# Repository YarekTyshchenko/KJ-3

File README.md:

KJ-3
====
Programming ATMega328 using an Arduino Micro
--------------------------------------------

All tutorials around programming ATMegas seem to revolve around removing the MCU from
an Arduino Uno and flashing it using normal methods. Since I don't have an Uno, and I
don't plan on getting one, it doesn't fit my needs, I need something that can go into
a breadboard, i've been having a really hard time collecting all the information on
making it work with a Micro and ISCP

So far i've got a few bits of information:

1. Upload ArduinoISP to your Mega, changing the SS definition to pin 10.
1. Modify boards.txt to include your breadboard configuration, or use Arduino Due 328
1. Add ArduinoISP as Micro definition to programmers.txt, found online somehwere
1. Compile and burn the chip with Shift+Ctrl-U (Shift click upload) to use the programmer...

This results in the code running on your new breadboarded MCU!

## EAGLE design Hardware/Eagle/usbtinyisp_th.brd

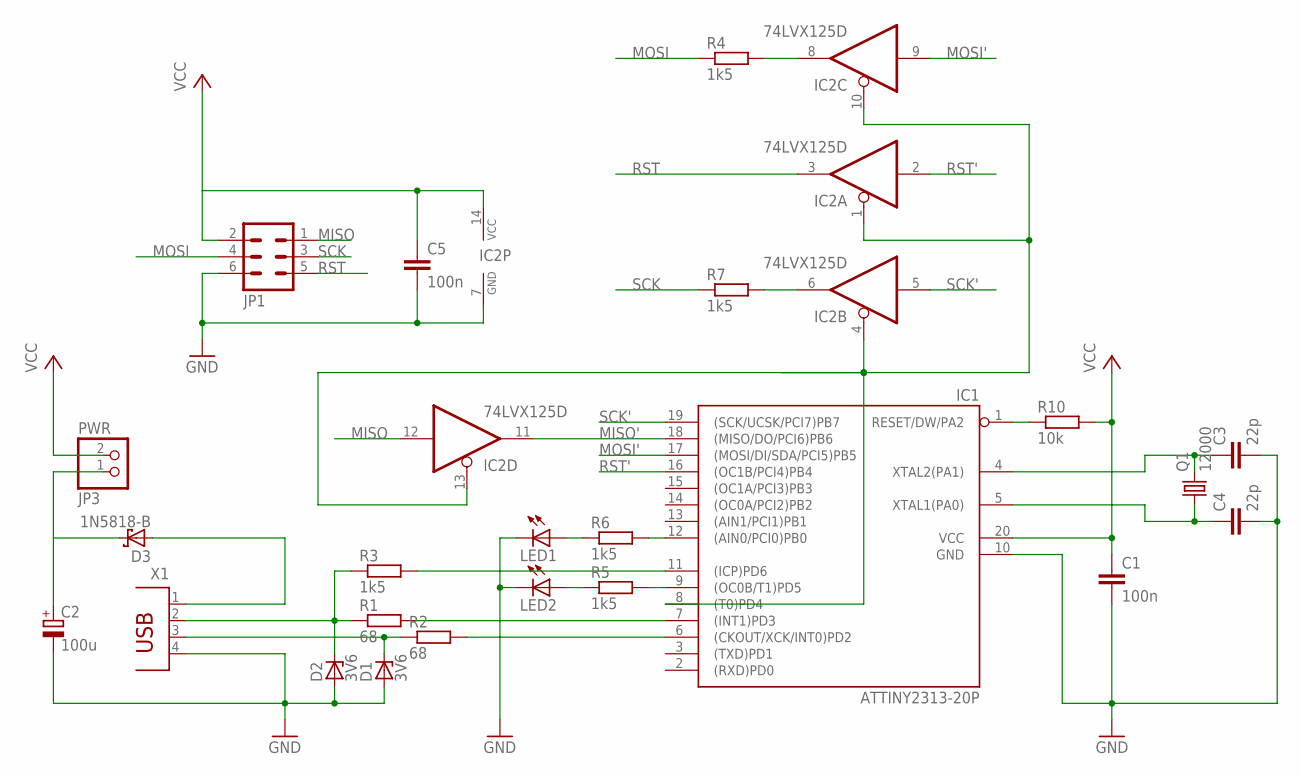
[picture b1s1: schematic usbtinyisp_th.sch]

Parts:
C1, C5: 100n; C025-025X050
C2: 100u; E2,5-6
C3, C4: 22p; C025-025X050
D1, D2: 3V6; DO35Z10
D3: 1N5818-B; DO41-7.6
IC1: ATTINY2313-20P; DIL20
IC2: 74LVX125D; DIL14
JP1: MA03-2
JP3: PWR; 1X02
LED1, LED2: LED5MM
Q1: 12000; HC49U-V
R1, R2: 68; 0204/7
R3, R4, R5, R6, R7: 1k5; 0204/7
R10: 10k; 0204/7
X1: PN61729

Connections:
GND: C1.2, C2.-, C3.2, C4.2, C5.2, D1.A, D2.A, IC1.10 (GND), IC2.7 (GND), JP1.6, LED1.K (C), LED2.K (C), X1.4
MISO: IC2.12 (I), JP1.1
MISO': IC1.18 ((MISO/DO/PCI6)PB6), IC2.11 (O)
MOSI: JP1.4, R4.1
MOSI': IC1.17 ((MOSI/DI/SDA/PCI5)PB5), IC2.9 (I)
unnamed: D2.C, R1.1, R3.1, X1.2
unnamed: D1.C, R2.1, X1.3
unnamed: IC1.7 ((INT1)PD3), R1.2
unnamed: C2.+, D3.C, JP3.1
unnamed: LED1.A, R6.1
unnamed: IC1.6 ((CKOUT/XCK/INT0)PD2), R2.2
unnamed: IC1.12 ((AIN0/PCI0)PB0), R6.2
unnamed: IC1.1 (RESET/DW/PA2), R10.1
unnamed: IC1.9 ((OC0B/T1)PD5), R5.2
unnamed: LED2.A, R5.1
unnamed: IC2.6 (O), R7.2
unnamed: IC2.8 (O), R4.2
unnamed: IC1.8 ((T0)PD4), IC2.1 (OE), IC2.4 (OE), IC2.10 (OE), IC2.13 (OE)
unnamed: IC1.11 ((ICP)PD6), R3.2
RST: IC2.3 (O), JP1.5
RST': IC1.16 ((OC1B/PCI4)PB4), IC2.2 (I)
SCK: JP1.3, R7.1
SCK': IC1.19 ((SCK/UCSK/PCI7)PB7), IC2.5 (I)
VBUS: D3.A, X1.1
VCC: C1.1, C5.1, IC1.20 (VCC), IC2.14 (VCC), JP1.2, JP3.2, R10.2
XTAL1: C4.1, IC1.5 (XTAL1(PA0)), Q1.1
XTAL2: C3.1, IC1.4 (XTAL2(PA1)), Q1.2

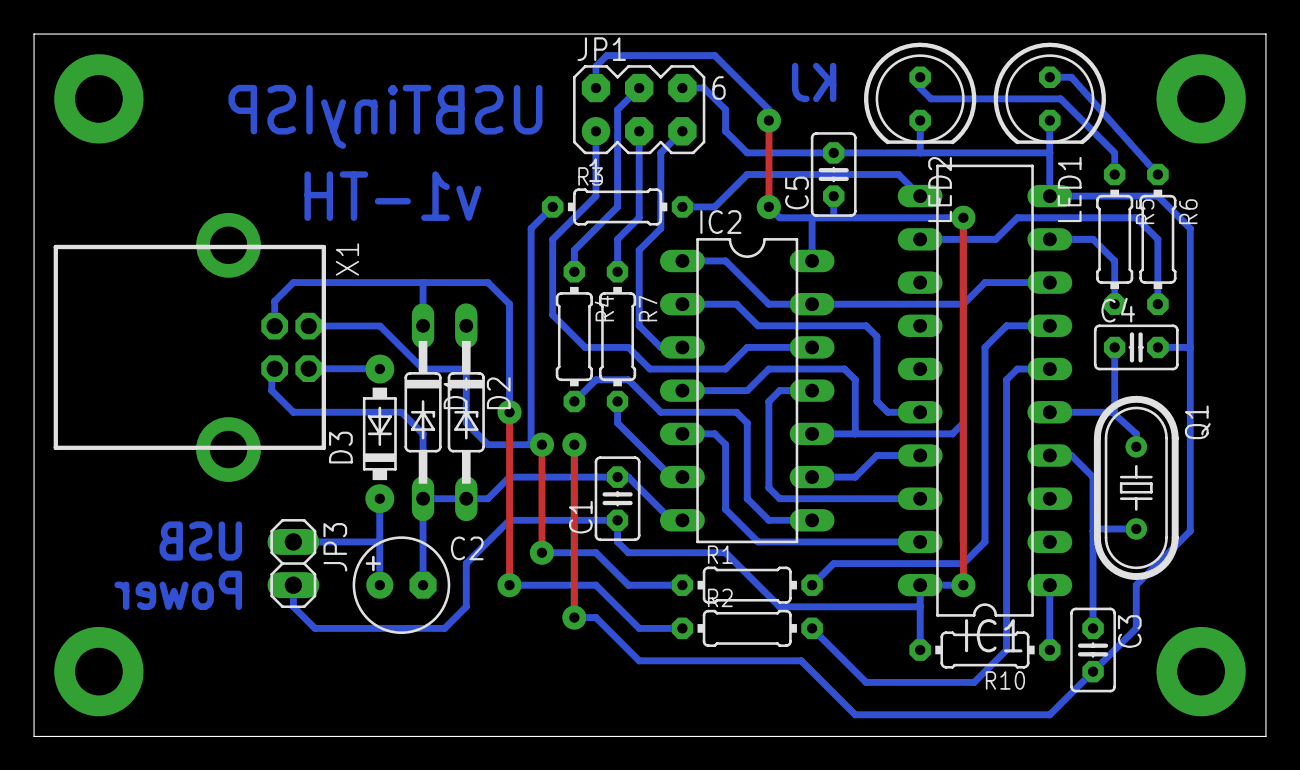
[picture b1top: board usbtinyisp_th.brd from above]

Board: 2 copper layers, 72.4 x 41.3 mm, 24 parts (0 on the bottom side), 27 nets.

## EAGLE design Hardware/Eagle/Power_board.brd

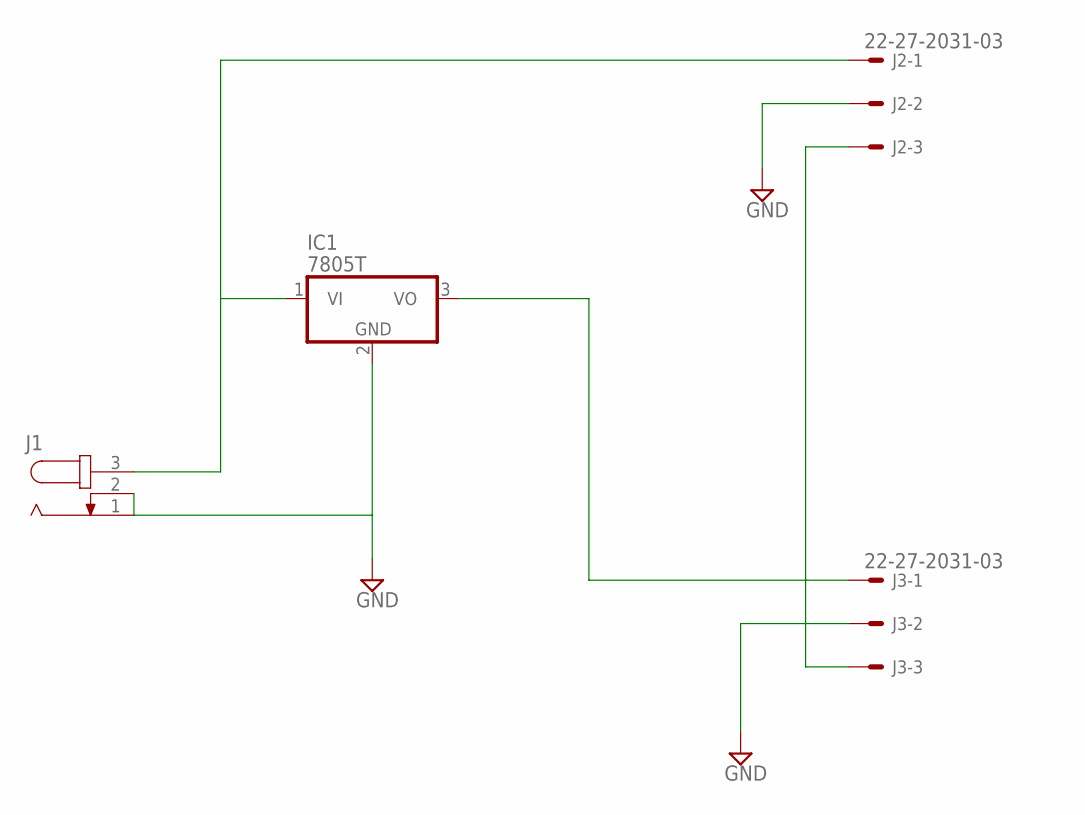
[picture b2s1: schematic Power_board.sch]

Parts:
IC1: 7805T; TO220H
J1: JACK-PLUG0; SPC4077
J2, J3: 22-27-2031-03; 6410-03

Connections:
GND: IC1.2 (GND), J1.1, J1.2, J2.2, J3.2
unnamed: IC1.1 (VI), J1.3, J2.1
unnamed: J2.3, J3.3
unnamed: IC1.3 (VO), J3.1

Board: 2 copper layers, 4 parts (0 on the bottom side), 4 nets, no tracks yet.

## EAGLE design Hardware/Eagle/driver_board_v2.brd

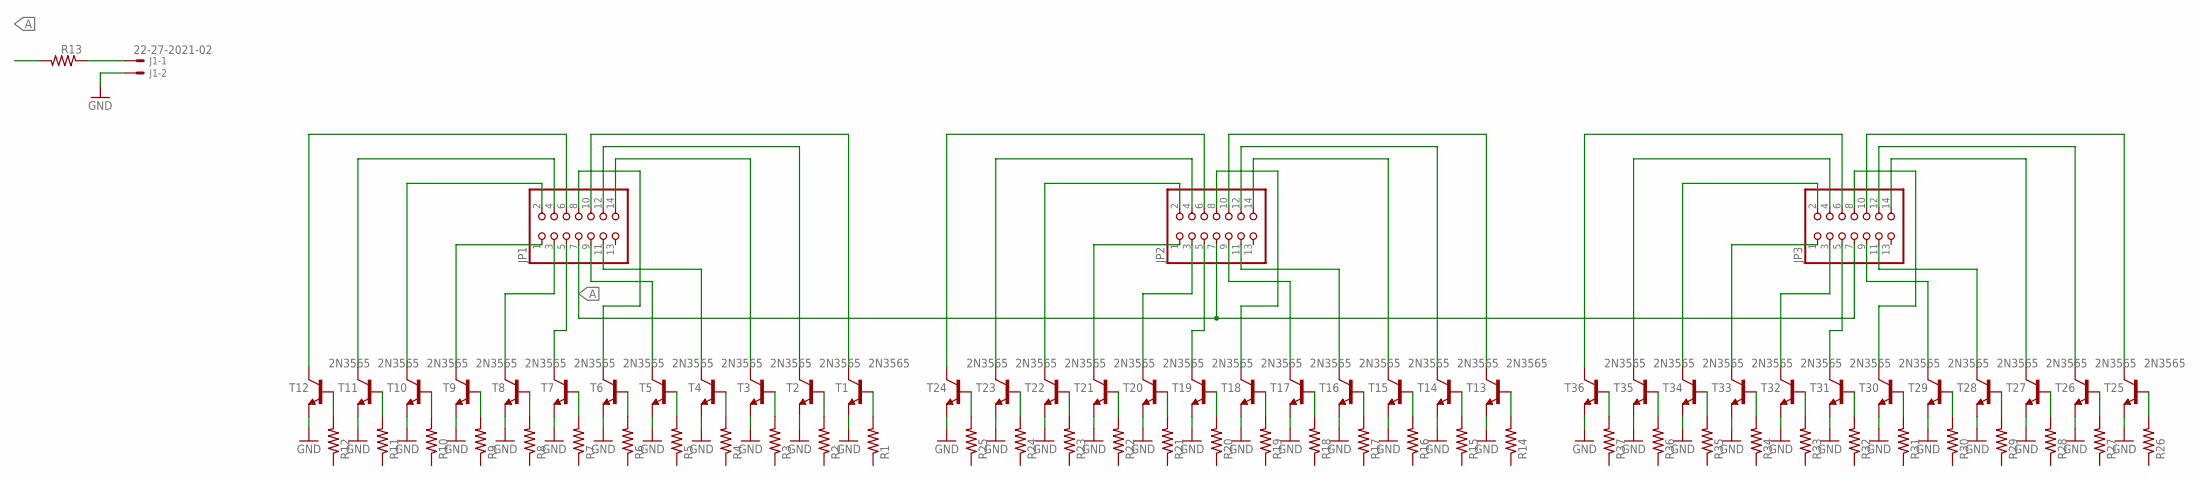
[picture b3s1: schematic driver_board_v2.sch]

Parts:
J1: 22-27-2021-02; 6410-02
JP1, JP2, JP3: PINHD-2X7; 2X07
R1, R2, R3, R4, R5, R6, R7, R8, R9, R10, R11, R12, R13, R14, R15, R16, R17, R18, R19, R20, R21, R22, R23, R24, R25, R26, R27, R28, R29, R30, R31, R32, R33, R34, R35, R36, R37: R-US_0204/7; 0204/7
T1, T2, T3, T4, T5, T6, T7, T8, T9, T10, T11, T12, T13, T14, T15, T16, T17, T18, T19, T20, T21, T22, T23, T24, T25, T26, T27, T28, T29, T30, T31, T32, T33, T34, T35, T36: 2N3565; TO92

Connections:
GND: J1.2, T1.3 (E), T2.3 (E), T3.3 (E), T4.3 (E), T5.3 (E), T6.3 (E), T7.3 (E), T8.3 (E), T9.3 (E), T10.3 (E), T11.3 (E), T12.3 (E), T13.3 (E), T14.3 (E), T15.3 (E), T16.3 (E), T17.3 (E), T18.3 (E), T19.3 (E), T20.3 (E), T21.3 (E), T22.3 (E), T23.3 (E), T24.3 (E), T25.3 (E), T26.3 (E), T27.3 (E), T28.3 (E), T29.3 (E), T30.3 (E), T31.3 (E), T32.3 (E), T33.3 (E), T34.3 (E), T35.3 (E), T36.3 (E)
unnamed: R12.2, T12.2 (B)
unnamed: R11.2, T11.2 (B)
unnamed: R10.2, T10.2 (B)
unnamed: R9.2, T9.2 (B)
unnamed: R8.2, T8.2 (B)
unnamed: R7.2, T7.2 (B)
unnamed: R6.2, T6.2 (B)
unnamed: R5.2, T5.2 (B)
unnamed: R4.2, T4.2 (B)
unnamed: R3.2, T3.2 (B)
unnamed: R2.2, T2.2 (B)
unnamed: R1.2, T1.2 (B)
unnamed: JP1.6, T12.1 (C)
unnamed: JP1.4, T11.1 (C)
unnamed: JP1.2, T10.1 (C)
unnamed: JP1.1, T9.1 (C)
unnamed: JP1.3, T8.1 (C)
unnamed: JP1.5, T7.1 (C)
unnamed: JP1.10, T1.1 (C)
unnamed: JP1.12, T2.1 (C)
unnamed: JP1.14, T3.1 (C)
unnamed: JP1.8, T6.1 (C)
unnamed: JP1.9, T5.1 (C)
unnamed: JP1.11, T4.1 (C)
unnamed: J1.1, R13.1
unnamed: R25.2, T24.2 (B)
unnamed: R24.2, T23.2 (B)
unnamed: R23.2, T22.2 (B)
unnamed: R22.2, T21.2 (B)
unnamed: R21.2, T20.2 (B)
unnamed: R20.2, T19.2 (B)
unnamed: R19.2, T18.2 (B)
unnamed: R18.2, T17.2 (B)
unnamed: R17.2, T16.2 (B)
unnamed: R16.2, T15.2 (B)
unnamed: R15.2, T14.2 (B)
unnamed: R14.2, T13.2 (B)
unnamed: JP2.6, T24.1 (C)
unnamed: JP2.4, T23.1 (C)
unnamed: JP2.2, T22.1 (C)
unnamed: JP2.1, T21.1 (C)
unnamed: JP2.3, T20.1 (C)
unnamed: JP2.5, T19.1 (C)
unnamed: JP2.10, T13.1 (C)
unnamed: JP2.12, T14.1 (C)
unnamed: JP2.14, T15.1 (C)
unnamed: JP2.8, T18.1 (C)
unnamed: JP2.9, T17.1 (C)
unnamed: JP2.11, T16.1 (C)
unnamed: R37.2, T36.2 (B)
unnamed: R36.2, T35.2 (B)
unnamed: R35.2, T34.2 (B)
unnamed: R34.2, T33.2 (B)
unnamed: R33.2, T32.2 (B)
unnamed: R32.2, T31.2 (B)
unnamed: R31.2, T30.2 (B)
unnamed: R30.2, T29.2 (B)
unnamed: R29.2, T28.2 (B)
unnamed: R28.2, T27.2 (B)
unnamed: R27.2, T26.2 (B)
unnamed: R26.2, T25.2 (B)
unnamed: JP3.6, T36.1 (C)
unnamed: JP3.4, T35.1 (C)
unnamed: JP3.2, T34.1 (C)
unnamed: JP3.1, T33.1 (C)
unnamed: JP3.3, T32.1 (C)
unnamed: JP3.5, T31.1 (C)
unnamed: JP3.10, T25.1 (C)
unnamed: JP3.12, T26.1 (C)
unnamed: JP3.14, T27.1 (C)
unnamed: JP3.8, T30.1 (C)
unnamed: JP3.9, T29.1 (C)
unnamed: JP3.11, T28.1 (C)

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
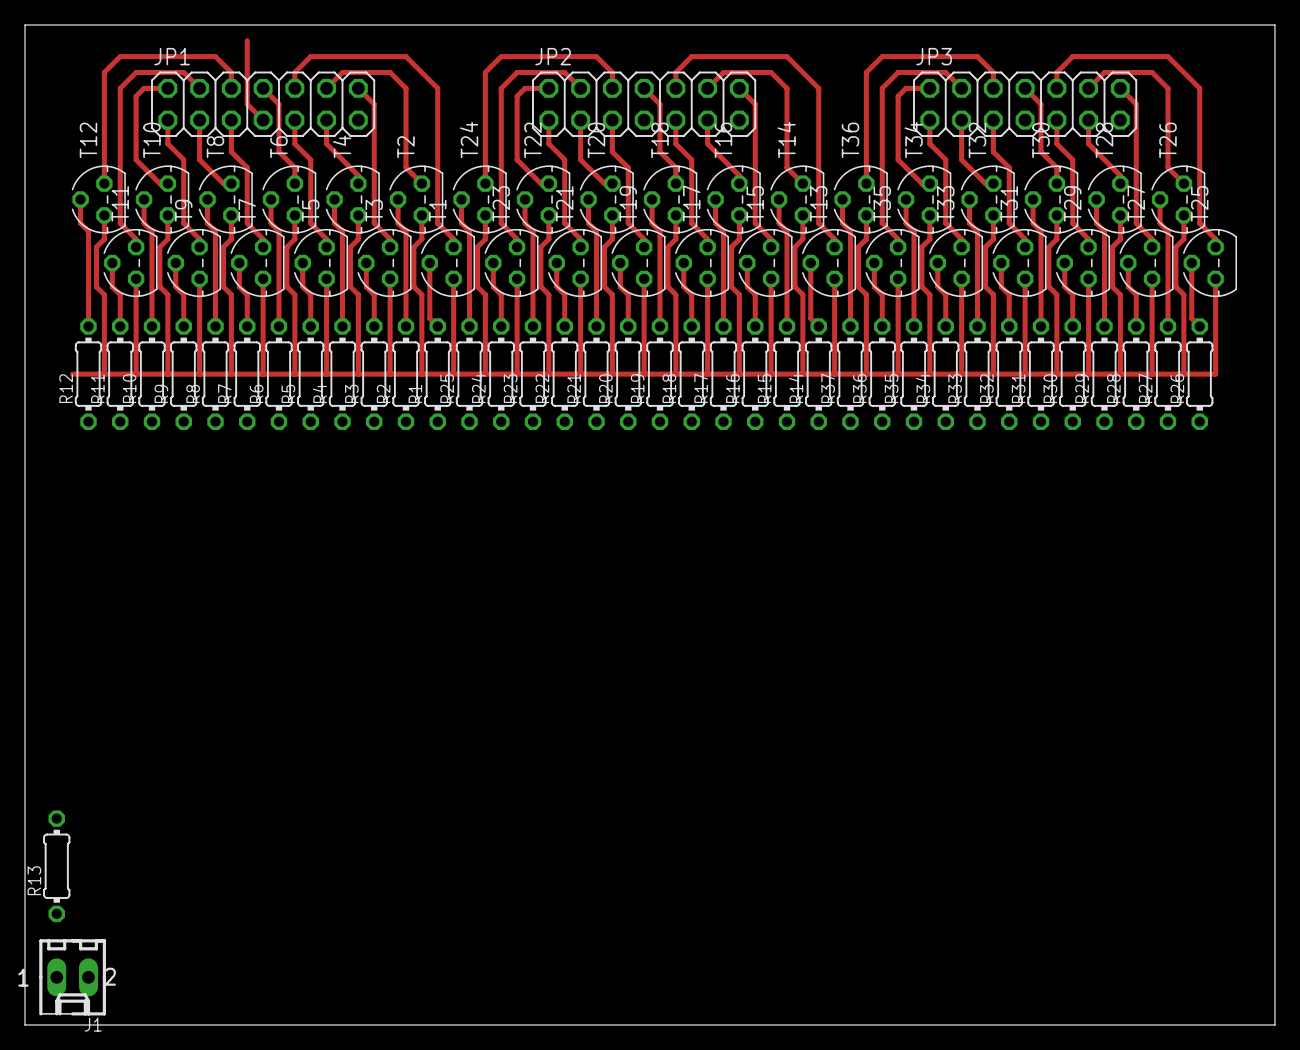
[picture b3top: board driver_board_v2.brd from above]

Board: 2 copper layers, 100.0 x 80.0 mm, 77 parts (0 on the bottom side), 75 nets.

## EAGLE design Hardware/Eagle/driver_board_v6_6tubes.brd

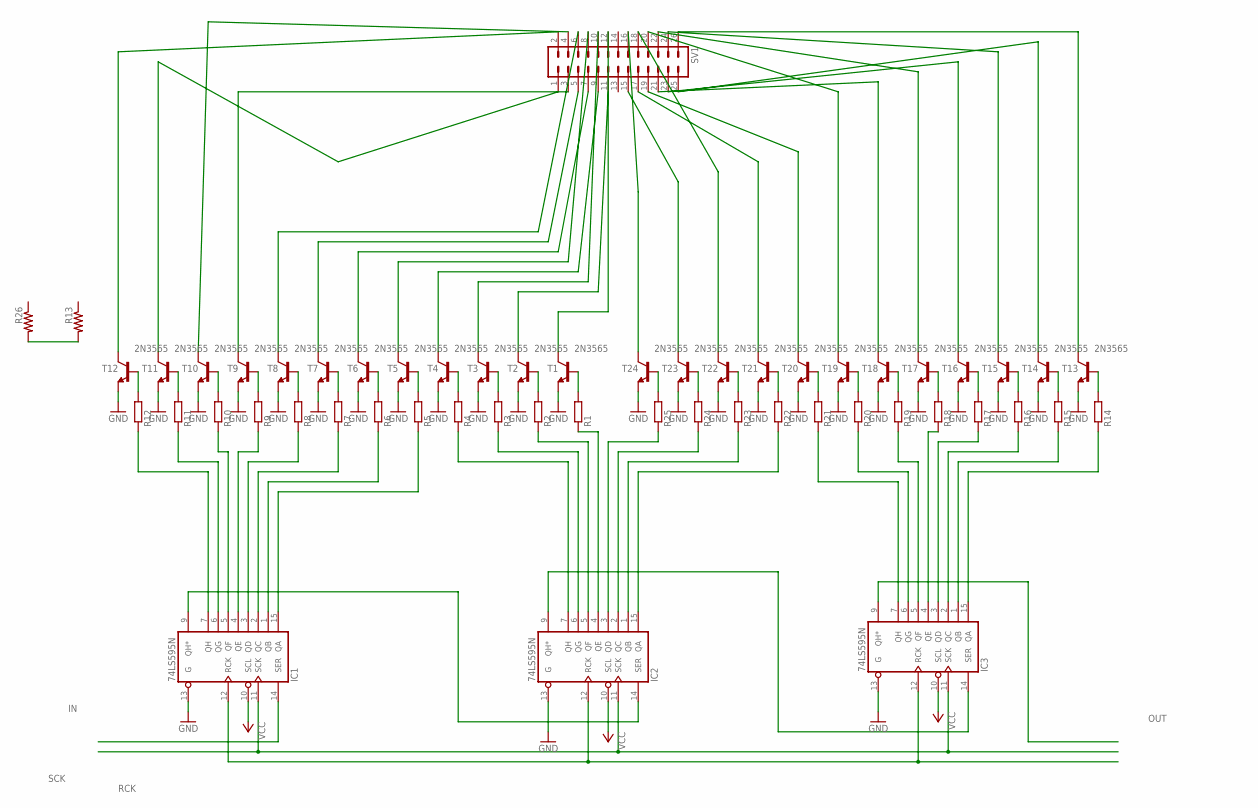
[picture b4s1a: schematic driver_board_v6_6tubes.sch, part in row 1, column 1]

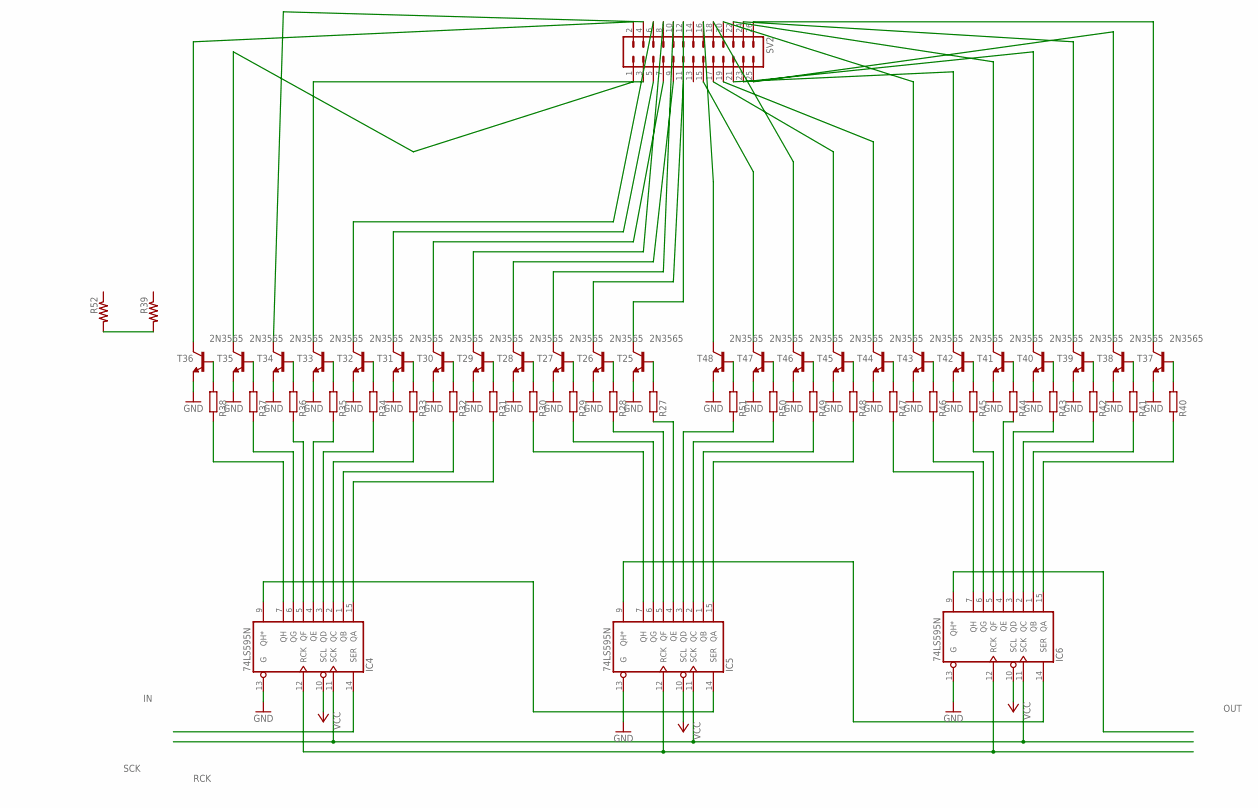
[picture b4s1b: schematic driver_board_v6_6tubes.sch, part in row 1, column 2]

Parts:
IC1, IC2, IC3, IC4, IC5, IC6: 74LS595N; DIL16
R1, R2, R3, R4, R5, R6, R7, R8, R9, R10, R11, R12, R14, R15, R16, R17, R18, R19, R20, R21, R22, R23, R24, R25, R27, R28, R29, R30, R31, R32, R33, R34, R35, R36, R37, R38, R40, R41, R42, R43, R44, R45, R46, R47, R48, R49, R50, R51: R-EU_0207/2V; 0207/2V
R13, R26, R39, R52: R-US_0204/7; 0204/7
SV1, SV2: MA13-2
T1, T2, T3, T4, T5, T6, T7, T8, T9, T10, T11, T12, T13, T14, T15, T16, T17, T18, T19, T20, T21, T22, T23, T24, T25, T26, T27, T28, T29, T30, T31, T32, T33, T34, T35, T36, T37, T38, T39, T40, T41, T42, T43, T44, T45, T46, T47, T48: 2N3565; TO92

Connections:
GND: IC1.8 (GND), IC1.13 (G), IC2.8 (GND), IC2.13 (G), IC3.8 (GND), IC3.13 (G), IC4.8 (GND), IC4.13 (G), IC5.8 (GND), IC5.13 (G), IC6.8 (GND), IC6.13 (G), T1.3 (E), T2.3 (E), T3.3 (E), T4.3 (E), T5.3 (E), T6.3 (E), T7.3 (E), T8.3 (E), T9.3 (E), T10.3 (E), T11.3 (E), T12.3 (E), T13.3 (E), T14.3 (E), T15.3 (E), T16.3 (E), T17.3 (E), T18.3 (E), T19.3 (E), T20.3 (E), T21.3 (E), T22.3 (E), T23.3 (E), T24.3 (E), T25.3 (E), T26.3 (E), T27.3 (E), T28.3 (E), T29.3 (E), T30.3 (E), T31.3 (E), T32.3 (E), T33.3 (E), T34.3 (E), T35.3 (E), T36.3 (E), T37.3 (E), T38.3 (E), T39.3 (E), T40.3 (E), T41.3 (E), T42.3 (E), T43.3 (E), T44.3 (E), T45.3 (E), T46.3 (E), T47.3 (E), T48.3 (E)
IN: IC1.14 (SER), IC4.14 (SER)
unnamed: R12.2, T12.2 (B)
unnamed: R11.2, T11.2 (B)
unnamed: R10.2, T10.2 (B)
unnamed: R9.2, T9.2 (B)
unnamed: R8.2, T8.2 (B)
unnamed: R7.2, T7.2 (B)
unnamed: R6.2, T6.2 (B)
unnamed: R5.2, T5.2 (B)
unnamed: R4.2, T4.2 (B)
unnamed: R3.2, T3.2 (B)
unnamed: R2.2, T2.2 (B)
unnamed: R1.2, T1.2 (B)
unnamed: SV1.12, T1.1 (C)
unnamed: R38.2, T36.2 (B)
unnamed: R37.2, T35.2 (B)
unnamed: SV1.3, T9.1 (C)
unnamed: SV1.6, T8.1 (C)
unnamed: SV1.5, T7.1 (C)
unnamed: R36.2, T34.2 (B)
unnamed: SV1.11, T2.1 (C)
unnamed: SV1.10, T3.1 (C)
unnamed: SV1.7, T6.1 (C)
unnamed: SV1.8, T5.1 (C)
unnamed: SV1.9, T4.1 (C)
unnamed: R35.2, T33.2 (B)
unnamed: R25.2, T24.2 (B)
unnamed: R24.2, T23.2 (B)
unnamed: R23.2, T22.2 (B)
unnamed: R22.2, T21.2 (B)
unnamed: R21.2, T20.2 (B)
unnamed: R20.2, T19.2 (B)
unnamed: R19.2, T18.2 (B)
unnamed: R18.2, T17.2 (B)
unnamed: R17.2, T16.2 (B)
unnamed: R16.2, T15.2 (B)
unnamed: R15.2, T14.2 (B)
unnamed: R14.2, T13.2 (B)
unnamed: SV1.16, T24.1 (C)
unnamed: SV1.15, T23.1 (C)
unnamed: SV1.18, T22.1 (C)
unnamed: SV1.17, T21.1 (C)
unnamed: SV1.19, T20.1 (C)
unnamed: SV1.20, T19.1 (C)
unnamed: SV1.26, T13.1 (C)
unnamed: SV1.25, T14.1 (C)
unnamed: SV1.24, T15.1 (C)
unnamed: SV1.21, T18.1 (C)
unnamed: SV1.22, T17.1 (C)
unnamed: SV1.23, T16.1 (C)
unnamed: R13.2, R26.2
unnamed: R34.2, T32.2 (B)
unnamed: IC1.9 (QH*), IC2.14 (SER)
unnamed: IC2.9 (QH*), IC3.14 (SER)
unnamed: R33.2, T31.2 (B)
unnamed: R32.2, T30.2 (B)
unnamed: SV1.2, T12.1 (C)
unnamed: R31.2, T29.2 (B)
unnamed: R30.2, T28.2 (B)
unnamed: SV1.1, T11.1 (C)
unnamed: SV1.4, T10.1 (C)
unnamed: R29.2, T27.2 (B)
unnamed: R28.2, T26.2 (B)
unnamed: R27.2, T25.2 (B)
unnamed: SV2.3, T33.1 (C)
unnamed: SV2.6, T32.1 (C)
unnamed: SV2.5, T31.1 (C)
unnamed: SV2.11, T26.1 (C)
unnamed: SV2.10, T27.1 (C)
unnamed: SV2.7, T30.1 (C)
unnamed: SV2.8, T29.1 (C)
unnamed: SV2.9, T28.1 (C)
unnamed: R51.2, T48.2 (B)
unnamed: R50.2, T47.2 (B)
unnamed: IC1.7 (QH), R12.1
unnamed: IC1.6 (QG), R11.1
unnamed: IC1.5 (QF), R10.1
unnamed: IC1.4 (QE), R9.1
unnamed: IC1.3 (QD), R8.1
unnamed: IC1.2 (QC), R7.1
unnamed: IC1.1 (QB), R6.1
unnamed: IC1.15 (QA), R5.1
unnamed: R49.2, T46.2 (B)
unnamed: IC2.7 (QH), R4.1
unnamed: IC2.6 (QG), R3.1
unnamed: IC2.5 (QF), R2.1
unnamed: IC2.4 (QE), R1.1
unnamed: IC2.3 (QD), R25.1
unnamed: IC2.2 (QC), R24.1
unnamed: IC2.1 (QB), R23.1
unnamed: IC2.15 (QA), R22.1
unnamed: IC3.7 (QH), R21.1
unnamed: IC3.6 (QG), R20.1
unnamed: IC3.5 (QF), R19.1
unnamed: IC3.4 (QE), R18.1
unnamed: IC3.3 (QD), R17.1
unnamed: IC3.2 (QC), R16.1
unnamed: IC3.1 (QB), R15.1
unnamed: IC3.15 (QA), R14.1
unnamed: R48.2, T45.2 (B)
unnamed: R47.2, T44.2 (B)
unnamed: R46.2, T43.2 (B)
unnamed: R45.2, T42.2 (B)
unnamed: R44.2, T41.2 (B)
unnamed: R43.2, T40.2 (B)
unnamed: R42.2, T39.2 (B)
unnamed: R41.2, T38.2 (B)
unnamed: R40.2, T37.2 (B)
unnamed: SV2.16, T48.1 (C)
unnamed: SV2.15, T47.1 (C)
unnamed: SV2.18, T46.1 (C)
unnamed: SV2.17, T45.1 (C)
unnamed: SV2.19, T44.1 (C)
unnamed: SV2.20, T43.1 (C)
unnamed: SV2.26, T37.1 (C)
unnamed: SV2.25, T38.1 (C)
unnamed: SV2.24, T39.1 (C)
unnamed: SV2.21, T42.1 (C)
unnamed: SV2.22, T41.1 (C)
unnamed: SV2.23, T40.1 (C)
unnamed: IC4.7 (QH), R38.1
unnamed: IC4.6 (QG), R37.1
unnamed: IC4.5 (QF), R36.1
unnamed: IC4.4 (QE), R35.1
unnamed: IC4.3 (QD), R34.1
unnamed: IC4.2 (QC), R33.1
unnamed: IC4.1 (QB), R32.1
unnamed: IC4.15 (QA), R31.1
unnamed: IC5.7 (QH), R30.1
unnamed: IC5.6 (QG), R29.1
unnamed: IC5.5 (QF), R28.1
unnamed: IC5.4 (QE), R27.1
unnamed: IC5.3 (QD), R51.1
unnamed: IC5.2 (QC), R50.1
unnamed: IC5.1 (QB), R49.1
unnamed: IC5.15 (QA), R48.1
unnamed: IC6.7 (QH), R47.1
unnamed: IC6.6 (QG), R46.1
unnamed: IC6.5 (QF), R45.1
unnamed: IC6.4 (QE), R44.1
unnamed: IC6.3 (QD), R43.1
unnamed: IC6.2 (QC), R42.1
unnamed: IC6.1 (QB), R41.1
unnamed: IC6.15 (QA), R40.1
unnamed: R39.2, R52.2
unnamed: IC4.9 (QH*), IC5.14 (SER)
unnamed: IC5.9 (QH*), IC6.14 (SER)
unnamed: SV2.12, T25.1 (C)
unnamed: SV2.2, T36.1 (C)
unnamed: SV2.1, T35.1 (C)
unnamed: SV2.4, T34.1 (C)
OUT: IC3.9 (QH*), IC6.9 (QH*)
RCK: IC1.12 (RCK), IC2.12 (RCK), IC3.12 (RCK), IC4.12 (RCK), IC5.12 (RCK), IC6.12 (RCK)
SCK: IC1.11 (SCK), IC2.11 (SCK), IC3.11 (SCK), IC4.11 (SCK), IC5.11 (SCK), IC6.11 (SCK)
VCC: IC1.10 (SCL), IC1.16 (VCC), IC2.10 (SCL), IC2.16 (VCC), IC3.10 (SCL), IC3.16 (VCC), IC4.10 (SCL), IC4.16 (VCC), IC5.10 (SCL), IC5.16 (VCC), IC6.10 (SCL), IC6.16 (VCC)

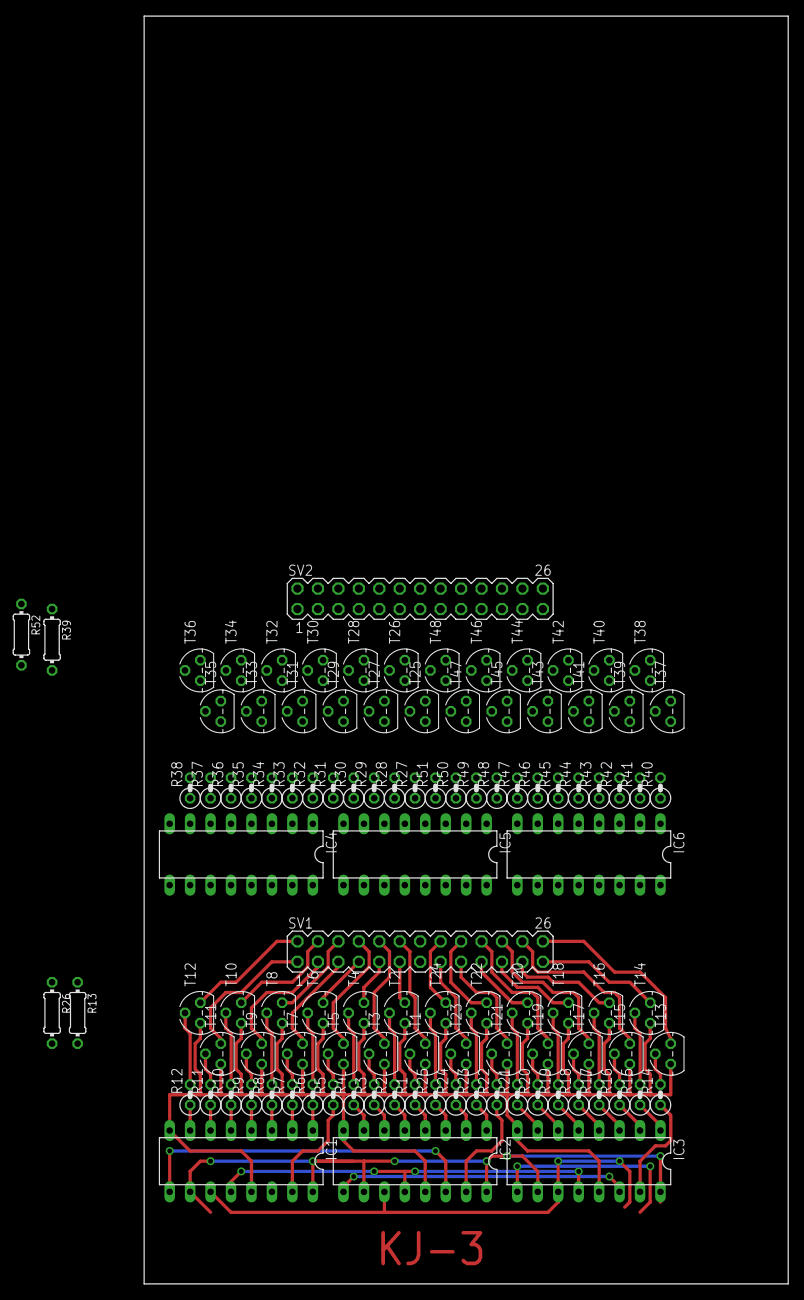
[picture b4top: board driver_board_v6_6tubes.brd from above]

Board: 2 copper layers, 80.0 x 157.5 mm, 108 parts (0 on the bottom side), 156 nets.
